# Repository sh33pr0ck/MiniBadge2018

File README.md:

# MiniBadge2018

Based on the minibadge by luke jenkins: https://github.com/lukejenkins/minibadge

Kicad files in the Minibadge folder.

I have never made a pcb or a schematic before so if it is flawed greatly then I apologize.  The minibadge receives power from the badge and uses an ATTiny85 to control the LEDs. I wanted to do something with IC2 but this is a new hobby and I didn't know what I was doing. 

The ATTiny85 will need to be programmed first. I used a Arduino MEGA 2560 but a UNO can be used. The ArduinoISP program that can be found in Examples didn't work for me and I found the following code to turn the Arduino into an ISP: 

https://github.com/adafruit/ArduinoISP/blob/master/ArduinoISP.ino

Load ArduinoISP onto the MEGA.

Add https://raw.githubusercontent.com/damellis/attiny/ide-1.6.x-boards-manager/package_damellis_attiny_index.json into Additional Boards Manager URLs and then add the attiny board.

With your MEGA still connected select ATTiny25/45/85 and select Processor ATTINY85.

Connect the following between the header on the minibadge and the MEGA:

Mini		MEGA

GND	-	GND

5V 	-	5V

MISO	-	50

MOSI	-	51

CS	-	53

SCK	-	52

Connect a 10uf capacitor between RESET and GND on the MEGA.

Select code and upload.

ATTiny Pins -

Pins 5, 4, and 3 control the LEDs.

I used code based on the following: https://cdn-learn.adafruit.com/downloads/pdf/adafruit-arduino-lesson-3-rgb-leds.pdf

Just updated the pins to the following:

const int redPin = 2;
const int greenPin = 3;
const int bluePin = 4;

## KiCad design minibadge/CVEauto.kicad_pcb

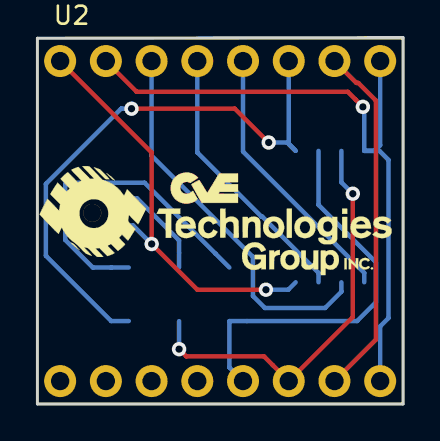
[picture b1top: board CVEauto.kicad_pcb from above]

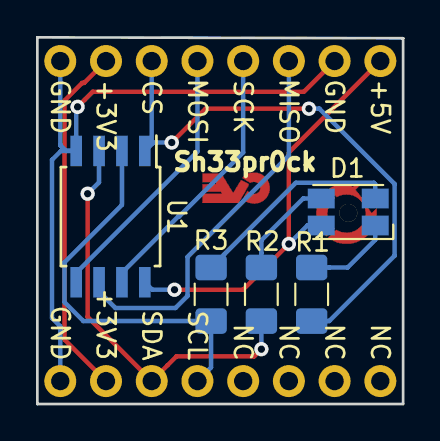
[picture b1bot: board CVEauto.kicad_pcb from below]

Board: 2 copper layers, 20.3 x 20.4 mm, 6 parts (5 on the bottom side), 12 nets.

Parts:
D1: LED_RAGB; LED_Avago_PLCC4_3.2x2.8mm_CW
R1, R2, R3: R_US; R_1206_3216Metric_Pad1.42x1.75mm_HandSolder
U1: ATtiny85-20SU; SOIJ-8_5.3x5.3mm_P1.27mm
U2: SAINTCON-Minibadge

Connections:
+3V3: U2.7, U2.15
+5V: D1.2, U1.8, U2.1
/PB0: U1.5, U2.5
/PB1: U1.6, U2.3
/PB2: U1.7, U2.4
/PB3: R3.2, U1.2, U2.13
/PB4: R2.2, U1.3, U2.14
/PB5: R1.2, U1.1, U2.6
GND: U1.4, U2.2, U2.8, U2.16
unnamed: D1.1, R1.1
unnamed: D1.3, R2.1
unnamed: D1.4, R3.1

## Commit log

2018-09-14 added content
